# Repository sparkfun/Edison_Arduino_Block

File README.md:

SparkFun Edison Arduino Block
=============================

[*SparkFun Edison Arduino Block(DEV-13036)*](https://www.sparkfun.com/products/13036)

Piggyback an Arduino onto your Edison with the Edison Arduino Pro board. This board features the same ATmega328P you'll find on Arduino Uno's, Pro's, and Pro Mini's. The 8-bit microcontroller workhorse is connected to the Edison via a selectable UART, so your Edison can interact with the Arduino over a serial interface.

The GPIO pins of the Arduino are all broken out to the familiar Pro Mini form factor. You can jump wires off of them to control LEDs, motors, or sensors. Or connect it straight up to a Pro Mini shield.

Repository Contents
-------------------
* **/Firmware** - Example Arduino sketch
* **/Hardware** - All Eagle design files (.brd, .sch)
* **/Production** - Test bed files and production panel files

License Information
--------------------
The hardware is released under [Creative Commons ShareAlike 4.0 International](https://creativecommons.org/licenses/by-sa/4.0/).
The code is beerware; if you see me (or any other SparkFun employee) at the local, and you've found our code helpful, please buy us a round!

Distributed as-is; no warranty is given.

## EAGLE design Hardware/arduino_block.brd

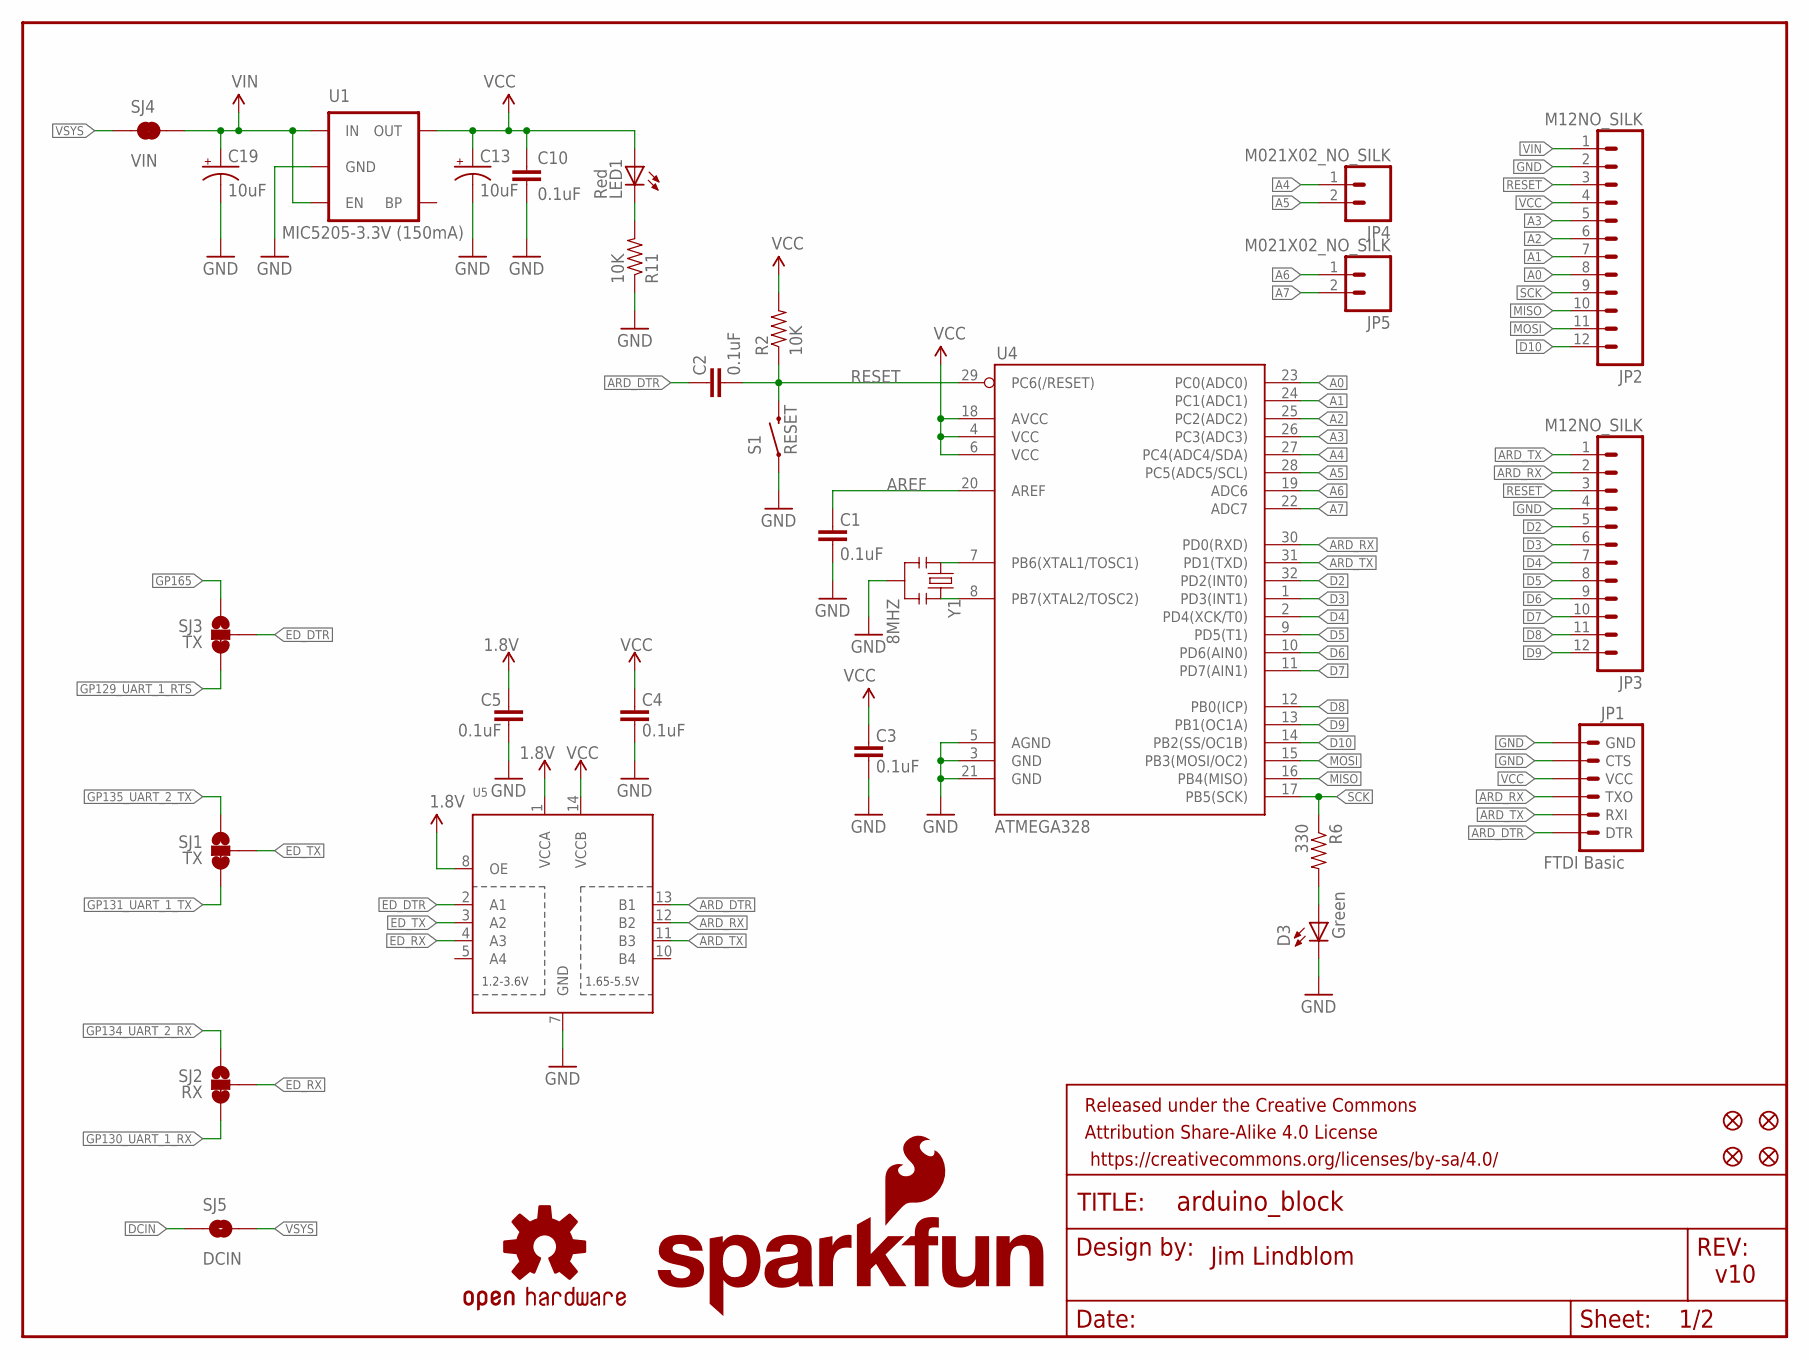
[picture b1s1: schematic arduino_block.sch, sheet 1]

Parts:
C1, C2, C3, C4, C5, C10: 0.1uF; 0603-CAP
C13, C19: 10uF; EIA3216
D3: Green; 0603-LED-ALT1
FID1, FID2, FID3, FID4: FIDUCIAL1X2; FIDUCIAL-1X2
FRAME1: FRAME-LETTER; CREATIVE_COMMONS
JP1: FTDI Basic; 1X06
JP2, JP3: M12NO_SILK; 1X12_NO_SILK
JP4, JP5: M021X02_NO_SILK; 1X02_NO_SILK
LED1: Red; 0603-LED-ALT1
LOGO1: OSHW-LOGOS; OSHW-LOGO-S
LOGO4: SFE_LOGO_NAME_FLAME.1_INCH; SFE_LOGO_NAME_FLAME_.1
R2, R11: 10K; 0603-RES
R6: 330; 0603-RES
S1: RESET; TACTILE_SWITCH-SMD-RIGHT-ANGLE
SJ1, SJ3: TX; PAD-JUMPER-3-2OF3_NC_BY_TRACE_YES_SILK_FULL_BOX
SJ2: RX; PAD-JUMPER-3-2OF3_NC_BY_TRACE_YES_SILK_FULL_BOX
SJ4: VIN; PAD-JUMPER-2-NC_BY_TRACE_YES_SILK
SJ5: DCIN; PAD-JUMPER-2-NO_YES_SILK
U1: MIC5205-3.3V (150mA); SOT23-5
U4: ATMEGA328; TQFP32-08
U5: TXB0104PWRSOIC14; SO14
Y1: 8MHZ; RESONATOR-SMD

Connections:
1.8V: C5.2, U5.1 (VCCA), U5.8 (OE); also elsewhere on the board
A0: JP2.8, U4.23 (PC0(ADC0))
A1: JP2.7, U4.24 (PC1(ADC1))
A2: JP2.6, U4.25 (PC2(ADC2))
A3: JP2.5, U4.26 (PC3(ADC3))
A4: JP4.1, U4.27 (PC4(ADC4/SDA))
A5: JP4.2, U4.28 (PC5(ADC5/SCL))
A6: JP5.1, U4.19 (ADC6)
A7: JP5.2, U4.22 (ADC7)
ARD_DTR: C2.2, JP1.1 (DTR), U5.13 (B1)
ARD_RX: JP1.3 (TXO), JP3.2, U4.30 (PD0(RXD)), U5.12 (B2)
ARD_TX: JP1.2 (RXI), JP3.1, U4.31 (PD1(TXD)), U5.11 (B3)
AREF: C1.2, U4.20 (AREF)
D2: JP3.5, U4.32 (PD2(INT0))
D3: JP3.6, U4.1 (PD3(INT1))
D4: JP3.7, U4.2 (PD4(XCK/T0))
D5: JP3.8, U4.9 (PD5(T1))
D6: JP3.9, U4.10 (PD6(AIN0))
D7: JP3.10, U4.11 (PD7(AIN1))
D8: JP3.11, U4.12 (PB0(ICP))
D9: JP3.12, U4.13 (PB1(OC1A))
D10: JP2.12, U4.14 (PB2(SS/OC1B))
DCIN: SJ5.1; also elsewhere on the board
ED_DTR: SJ3.2, U5.2 (A1)
ED_RX: SJ2.2, U5.4 (A3)
ED_TX: SJ1.2, U5.3 (A2)
GND: C1.1, C3.1, C4.1, C5.1, C10.2, C13.C (-), C19.C (-), D3.C, JP1.5 (CTS), JP1.6 (GND), JP2.2, JP3.4, R11.1, S1.1, U1.2 (GND), U4.3 (GND), U4.5 (AGND), U4.21 (GND), U5.7 (GND), Y1.2; also elsewhere on the board
GP129_UART_1_RTS: SJ3.3; also elsewhere on the board
GP130_UART_1_RX: SJ2.3; also elsewhere on the board
GP131_UART_1_TX: SJ1.3; also elsewhere on the board
GP134_UART_2_RX: SJ2.1; also elsewhere on the board
GP135_UART_2_TX: SJ1.1; also elsewhere on the board
GP165: SJ3.1; also elsewhere on the board
MISO: JP2.10, U4.16 (PB4(MISO))
MOSI: JP2.11, U4.15 (PB3(MOSI/OC2))
unnamed: U4.8 (PB7(XTAL2/TOSC2)), Y1.3
unnamed: U4.7 (PB6(XTAL1/TOSC1)), Y1.1
unnamed: LED1.C, R11.2
unnamed: D3.A, R6.2
RESET: C2.1, JP2.3, JP3.3, R2.1, S1.2, U4.29 (PC6(/RESET))
SCK: JP2.9, R6.1, U4.17 (PB5(SCK))
VCC: C3.2, C4.2, C10.1, C13.A (+), JP1.4 (VCC), JP2.4, LED1.A, R2.2, U1.5 (OUT), U4.4 (VCC), U4.6 (VCC), U4.18 (AVCC), U5.14 (VCCB)
VIN: C19.A (+), JP2.1, SJ4.2, U1.1 (IN), U1.3 (EN)
VSYS: SJ4.1, SJ5.2; also elsewhere on the board

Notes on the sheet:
v10
Jim Lindblom

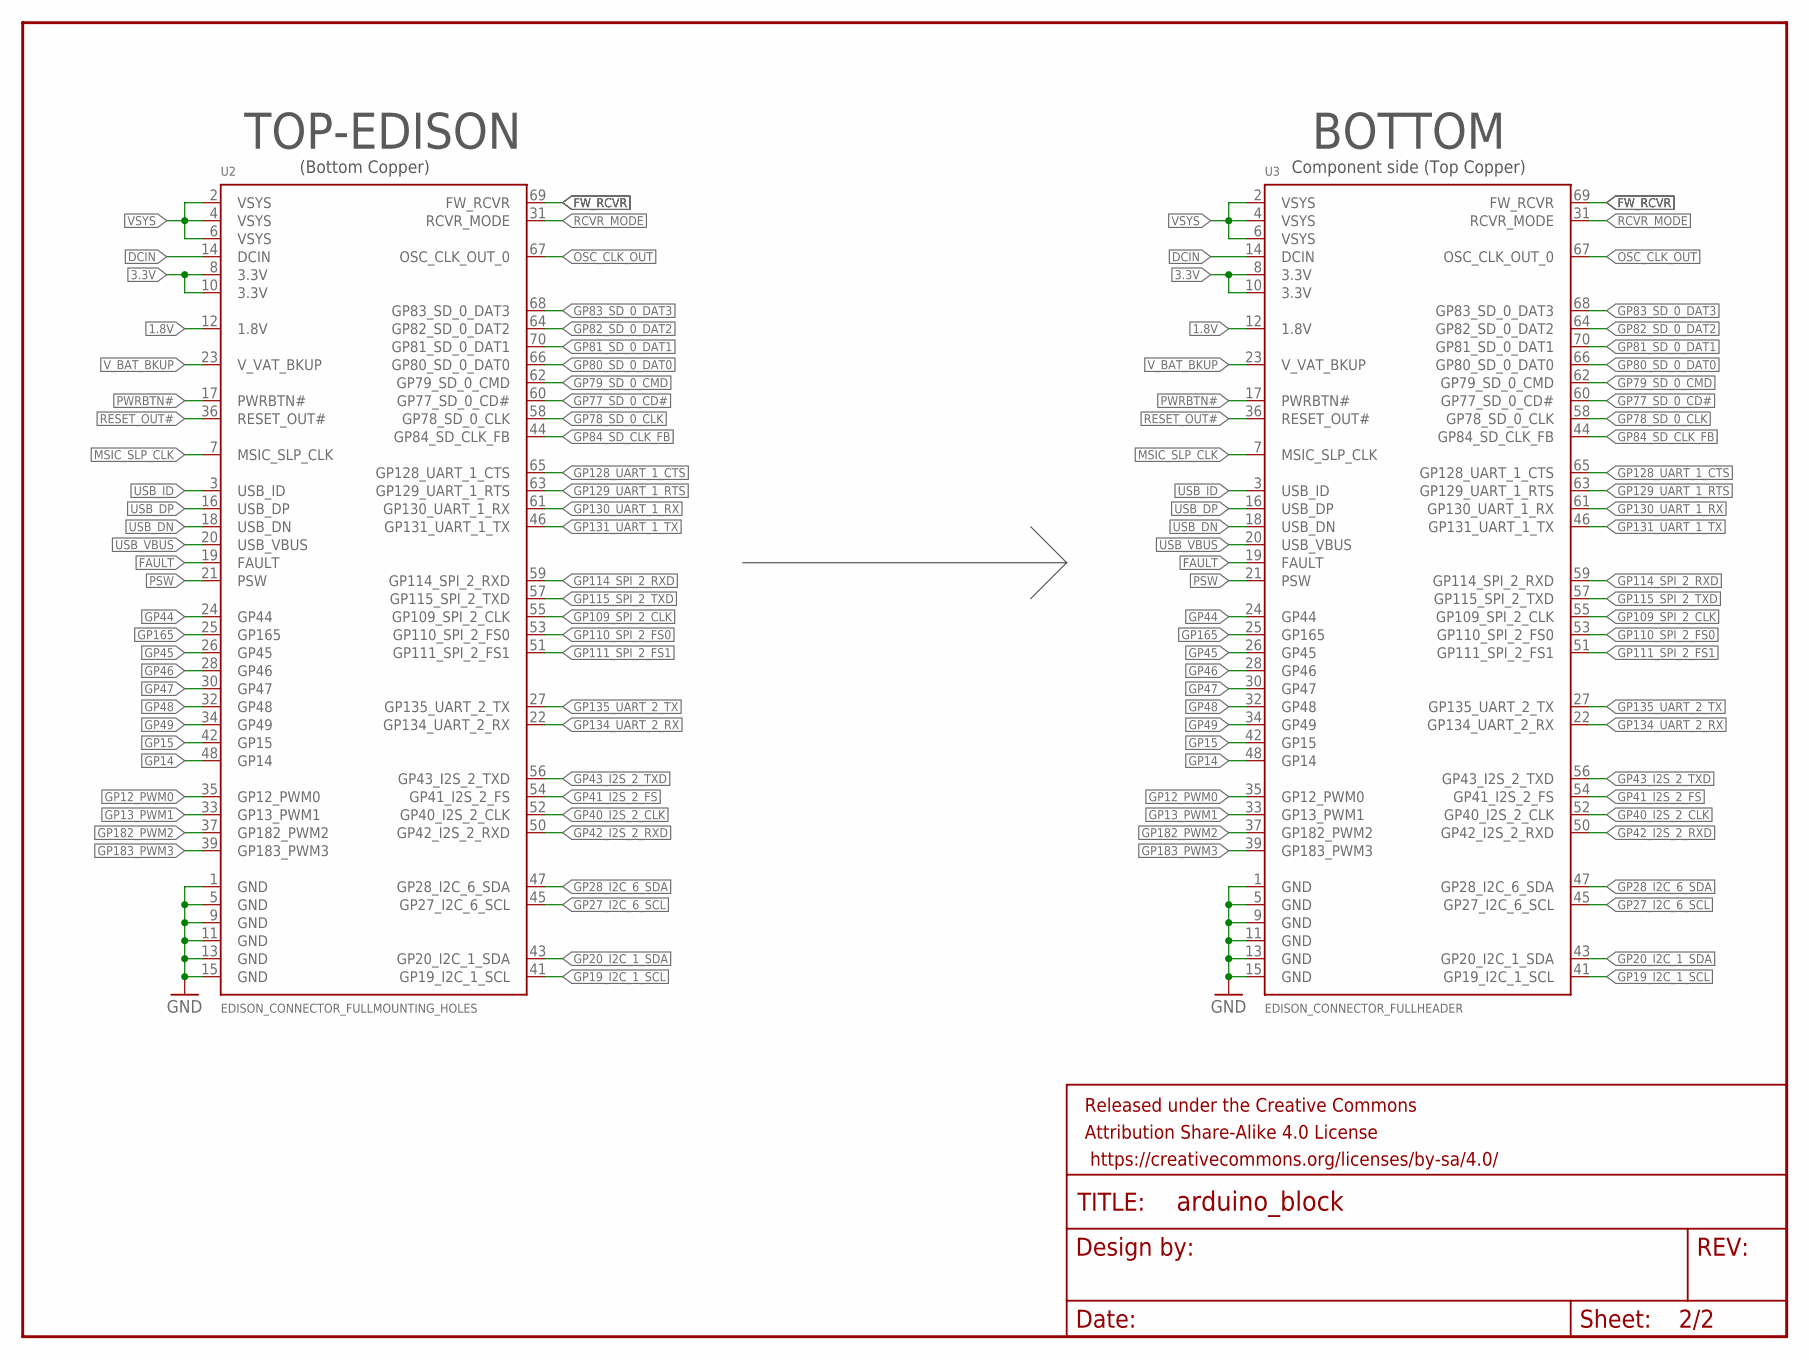
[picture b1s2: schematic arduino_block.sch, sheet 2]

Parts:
FRAME2: FRAME-LETTER; CREATIVE_COMMONS
U2: EDISON_CONNECTOR_FULLMOUNTING_HOLES; EDISON_DAUGHTER
U3: EDISON_CONNECTOR_FULLHEADER; DF40C-70DP-0.4(51)

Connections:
1.8V: U2.12 (1.8V), U3.12 (1.8V); also elsewhere on the board
3.3V: U2.8 (3.3V), U2.10 (3.3V), U3.8 (3.3V), U3.10 (3.3V)
DCIN: U2.14 (DCIN), U3.14 (DCIN); also elsewhere on the board
FAULT: U2.19 (FAULT), U3.19 (FAULT)
FW_RCVR: U2.69 (FW_RCVR), U3.69 (FW_RCVR)
GND: U2.1 (GND), U2.5 (GND), U2.9 (GND), U2.11 (GND), U2.13 (GND), U2.15 (GND), U3.1 (GND), U3.5 (GND), U3.9 (GND), U3.11 (GND), U3.13 (GND), U3.15 (GND); also elsewhere on the board
GP12_PWM0: U2.35 (GP12_PWM0), U3.35 (GP12_PWM0)
GP13_PWM1: U2.33 (GP13_PWM1), U3.33 (GP13_PWM1)
GP14: U2.48 (GP14), U3.48 (GP14)
GP15: U2.42 (GP15), U3.42 (GP15)
GP19_I2C_1_SCL: U2.41 (GP19_I2C_1_SCL), U3.41 (GP19_I2C_1_SCL)
GP20_I2C_1_SDA: U2.43 (GP20_I2C_1_SDA), U3.43 (GP20_I2C_1_SDA)
GP27_I2C_6_SCL: U2.45 (GP27_I2C_6_SCL), U3.45 (GP27_I2C_6_SCL)
GP28_I2C_6_SDA: U2.47 (GP28_I2C_6_SDA), U3.47 (GP28_I2C_6_SDA)
GP40_I2S_2_CLK: U2.52 (GP40_I2S_2_CLK), U3.52 (GP40_I2S_2_CLK)
GP41_I2S_2_FS: U2.54 (GP41_I2S_2_FS), U3.54 (GP41_I2S_2_FS)
GP42_I2S_2_RXD: U2.50 (GP42_I2S_2_RXD), U3.50 (GP42_I2S_2_RXD)
GP43_I2S_2_TXD: U2.56 (GP43_I2S_2_TXD), U3.56 (GP43_I2S_2_TXD)
GP44: U2.24 (GP44), U3.24 (GP44)
GP45: U2.26 (GP45), U3.26 (GP45)
GP46: U2.28 (GP46), U3.28 (GP46)
GP47: U2.30 (GP47), U3.30 (GP47)
GP48: U2.32 (GP48), U3.32 (GP48)
GP49: U2.34 (GP49), U3.34 (GP49)
GP77_SD_0_CD#: U2.60 (GP77_SD_0_CD#), U3.60 (GP77_SD_0_CD#)
GP78_SD_0_CLK: U2.58 (GP78_SD_0_CLK), U3.58 (GP78_SD_0_CLK)
GP79_SD_0_CMD: U2.62 (GP79_SD_0_CMD), U3.62 (GP79_SD_0_CMD)
GP80_SD_0_DAT0: U2.66 (GP80_SD_0_DAT0), U3.66 (GP80_SD_0_DAT0)
GP81_SD_0_DAT1: U2.70 (GP81_SD_0_DAT1), U3.70 (GP81_SD_0_DAT1)
GP82_SD_0_DAT2: U2.64 (GP82_SD_0_DAT2), U3.64 (GP82_SD_0_DAT2)
GP83_SD_0_DAT3: U2.68 (GP83_SD_0_DAT3), U3.68 (GP83_SD_0_DAT3)
GP84_SD_CLK_FB: U2.44 (GP84_SD_CLK_FB), U3.44 (GP84_SD_CLK_FB)
GP109_SPI_2_CLK: U2.55 (GP109_SPI_2_CLK), U3.55 (GP109_SPI_2_CLK)
GP110_SPI_2_FS0: U2.53 (GP110_SPI_2_FS0), U3.53 (GP110_SPI_2_FS0)
GP111_SPI_2_FS1: U2.51 (GP111_SPI_2_FS1), U3.51 (GP111_SPI_2_FS1)
GP114_SPI_2_RXD: U2.59 (GP114_SPI_2_RXD), U3.59 (GP114_SPI_2_RXD)
GP115_SPI_2_TXD: U2.57 (GP115_SPI_2_TXD), U3.57 (GP115_SPI_2_TXD)
GP128_UART_1_CTS: U2.65 (GP128_UART_1_CTS), U3.65 (GP128_UART_1_CTS)
GP129_UART_1_RTS: U2.63 (GP129_UART_1_RTS), U3.63 (GP129_UART_1_RTS); also elsewhere on the board
GP130_UART_1_RX: U2.61 (GP130_UART_1_RX), U3.61 (GP130_UART_1_RX); also elsewhere on the board
GP131_UART_1_TX: U2.46 (GP131_UART_1_TX), U3.46 (GP131_UART_1_TX); also elsewhere on the board
GP134_UART_2_RX: U2.22 (GP134_UART_2_RX), U3.22 (GP134_UART_2_RX); also elsewhere on the board
GP135_UART_2_TX: U2.27 (GP135_UART_2_TX), U3.27 (GP135_UART_2_TX); also elsewhere on the board
GP165: U2.25 (GP165), U3.25 (GP165); also elsewhere on the board
GP182_PWM2: U2.37 (GP182_PWM2), U3.37 (GP182_PWM2)
GP183_PWM3: U2.39 (GP183_PWM3), U3.39 (GP183_PWM3)
MSIC_SLP_CLK: U2.7 (MSIC_SLP_CLK), U3.7 (MSIC_SLP_CLK)
OSC_CLK_OUT: U2.67 (OSC_CLK_OUT_0), U3.67 (OSC_CLK_OUT_0)
PSW: U2.21 (PSW), U3.21 (PSW)
PWRBTN#: U2.17 (PWRBTN#), U3.17 (PWRBTN#)
RCVR_MODE: U2.31 (RCVR_MODE), U3.31 (RCVR_MODE)
RESET_OUT#: U2.36 (RESET_OUT#), U3.36 (RESET_OUT#)
USB_DN: U2.18 (USB_DN), U3.18 (USB_DN)
USB_DP: U2.16 (USB_DP), U3.16 (USB_DP)
USB_ID: U2.3 (USB_ID), U3.3 (USB_ID)
USB_VBUS: U2.20 (USB_VBUS), U3.20 (USB_VBUS)
VSYS: U2.2 (VSYS), U2.4 (VSYS), U2.6 (VSYS), U3.2 (VSYS), U3.4 (VSYS), U3.6 (VSYS); also elsewhere on the board
V_BAT_BKUP: U2.23 (V_VAT_BKUP), U3.23 (V_VAT_BKUP)

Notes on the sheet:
TOP-EDISON
BOTTOM
Component side (Top Copper)
(Bottom Copper)

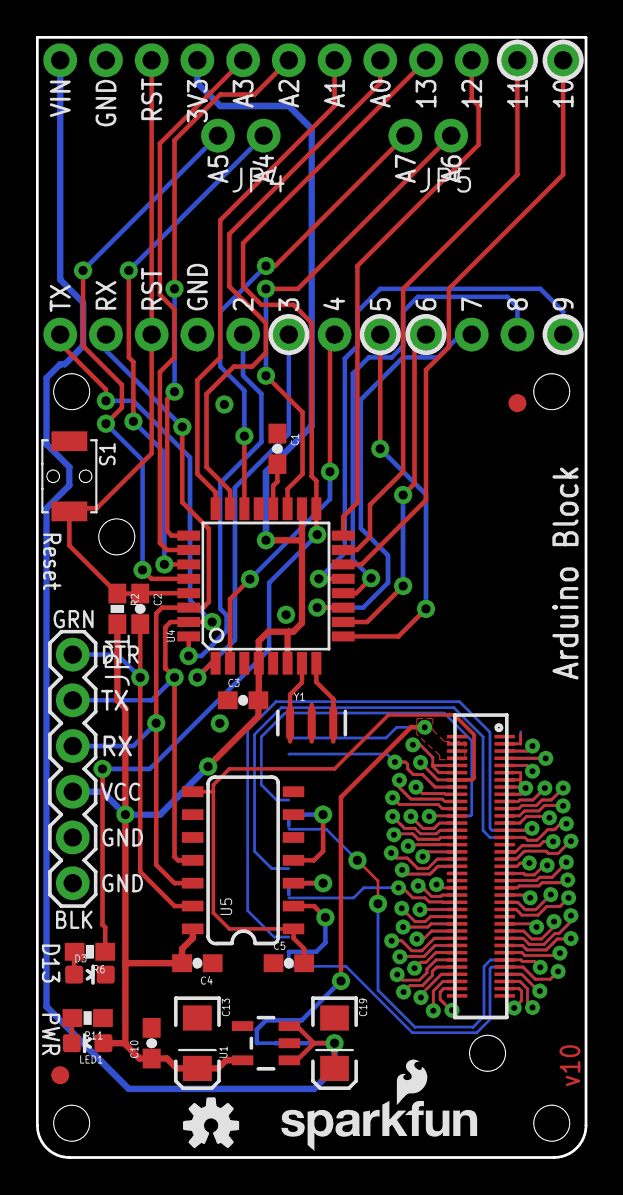
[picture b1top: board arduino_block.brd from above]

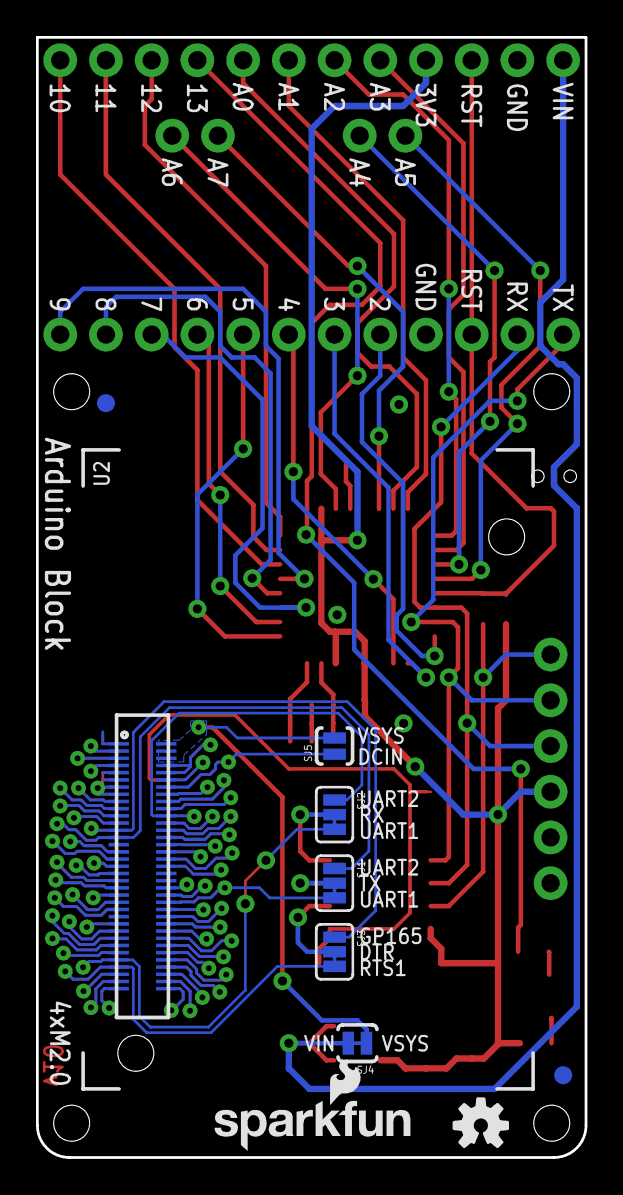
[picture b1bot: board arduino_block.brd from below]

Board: 2 copper layers, 30.5 x 62.2 mm, 40 parts (11 on the bottom side), 92 nets.

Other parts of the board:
LOGO2: OSHW-LOGOS; OSHW-LOGO-S
LOGO3: SFE_LOGO_NAME_FLAME.1_INCH; SFE_LOGO_NAME_FLAME_.1

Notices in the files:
parts and their libraries:
SparkFun-Aesthetics: Licensing: Creative Commons ShareAlike 4.0 International - https://creativecommons.org/licenses/by-sa/4.0
SparkFun-Aesthetics: Released under the Creative Commons Attribution Share-Alike 4.0 License
SparkFun-Aesthetics: Released under the Creative Commons
